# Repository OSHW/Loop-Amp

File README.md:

# Loop-Amp
RCHourglass Antenna Loop amplifier

SMD version of Antenna Loop amplifier used by Cano Decoder or others RC timing systems

CAD type: EAGLE

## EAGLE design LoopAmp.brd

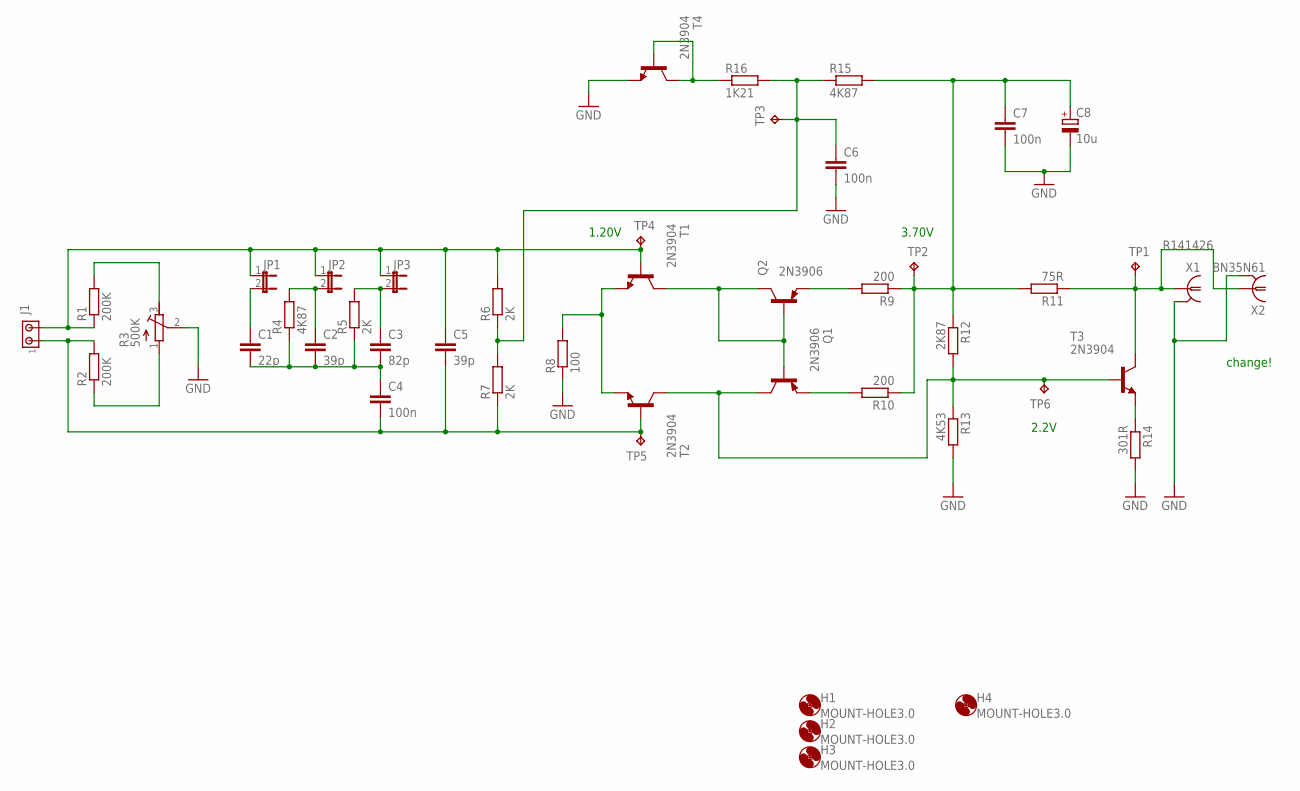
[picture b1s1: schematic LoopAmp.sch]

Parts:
C1: 22p; C0805
C2, C5: 39p; C0805
C3: 82p; C0805
C4, C6, C7: 100n; C0805
C8: 10u; PANASONIC_C
H1, H2, H3, H4: MOUNT-HOLE3.0; 3,0
J1: MTA02-156; 1X2MTA
JP1, JP2, JP3: JP1E; JP1
Q1, Q2: 2N3906; TO92
R1, R2: 200K; R0805
R3: 500K; RTRIM64W
R4, R15: 4K87; R0805
R5, R6, R7: 2K; R0805
R8: 100; R0805
R9, R10: 200; R0805
R11: 75R; R0805
R12: 2K87; R0805
R13: 4K53; R0805
R14: 301R; R0805
R16: 1K21; R0805
T1, T2, T3, T4: 2N3904; TO92
TP1, TP2, TP3, TP4, TP5, TP6: 4.18V>; P1-13
X1: R141426
X2: BN35N61; B35N61

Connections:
GND: C6.2, C7.2, C8.-, R3.2 (S), R8.1, R13.2, R14.2, T4.3 (E), X1.2, X1.3 (2), X1.4 (2), X1.5 (2), X2.2, X2.3 (2), X2.4 (2), X2.5 (2)
unnamed: C4.2, C5.2, J1.1, R2.2, R7.1, T2.2 (B), TP5.TP
unnamed: C5.1, J1.2, JP1.1, JP2.1, JP3.1, R1.1, R6.2, T1.2 (B), TP4.TP
unnamed: R2.1, R3.1 (A)
unnamed: C1.1, JP1.2
unnamed: C2.1, JP2.2, R4.2
unnamed: C3.1, JP3.2, R5.2
unnamed: C1.2, C2.2, C3.2, C4.1, R4.1, R5.1
unnamed: R1.2, R3.3 (E)
unnamed: R8.2, T1.3 (E), T2.3 (E)
unnamed: Q1.2 (B), Q2.1 (C), Q2.2 (B), T1.1 (C)
unnamed: R11.1, T3.1 (C), TP1.TP, X1.1, X2.1
unnamed: C7.1, C8.+, R9.1, R10.1, R11.2, R12.1, R15.2, TP2.TP
unnamed: Q2.3 (E), R9.2
unnamed: Q1.3 (E), R10.2
unnamed: Q1.1 (C), R12.2, R13.1, T2.1 (C), T3.2 (B), TP6.TP
unnamed: R14.1, T3.3 (E)
unnamed: C6.1, R6.1, R7.2, R15.1, R16.2, TP3.TP
unnamed: R16.1, T4.1 (C), T4.2 (B)

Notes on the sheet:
2.2V
1.20V
3.70V
change!

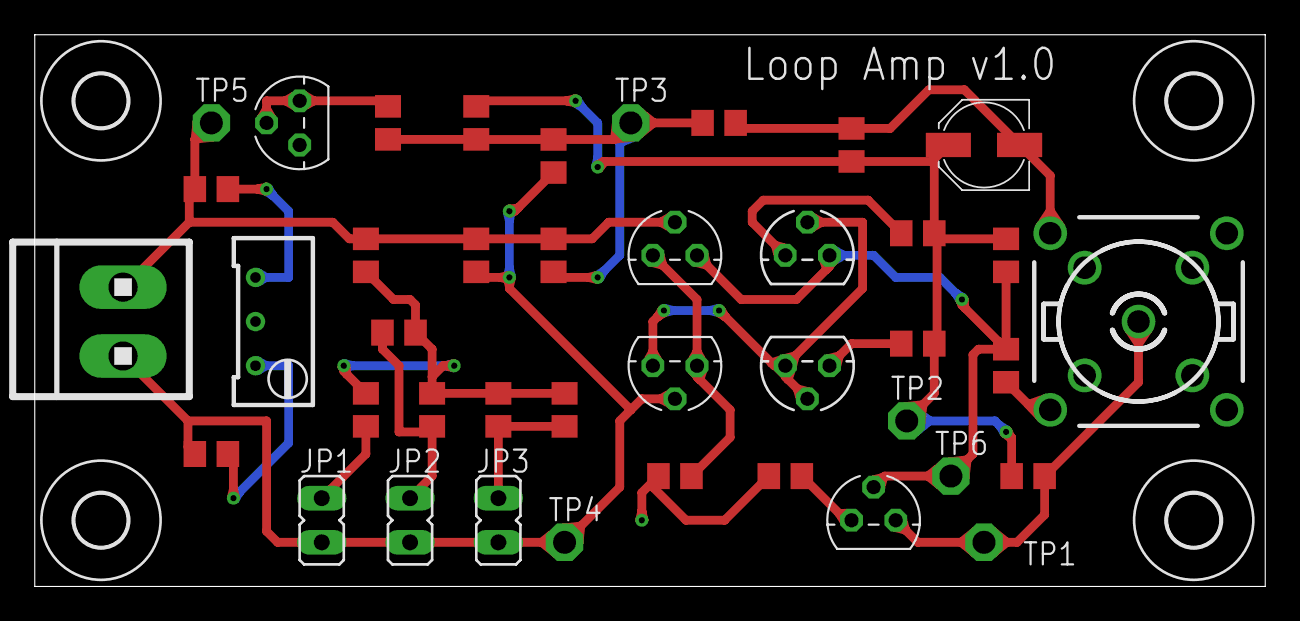
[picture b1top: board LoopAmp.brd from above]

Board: 2 copper layers, 70.8 x 31.7 mm, 46 parts (0 on the bottom side), 19 nets.

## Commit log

2018-05-03 :confetti_ball: Added .gitattributes & .gitignore files
